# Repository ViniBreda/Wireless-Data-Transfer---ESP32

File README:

# Wireless Data Transfer Between two ESP32 - DOIT Devkit 1

* File upload via bluetooth available BUT VERY SLOW;
* The goal is to send a 500KB file from one ESP32 to another, atleast 100m apart;
* The PCB was of the transmission board was designed considering up to eight I²C devices connected to it so it works as a DataLogger;
* The receiver PCB is just a normal DOIT Devkit 1 remake to learn how to use KiCad;
* This is just a concept, not all funcionalities will be developed/tested as the main goal is to send a file over a Wireless Conection, one of them being battery powered.

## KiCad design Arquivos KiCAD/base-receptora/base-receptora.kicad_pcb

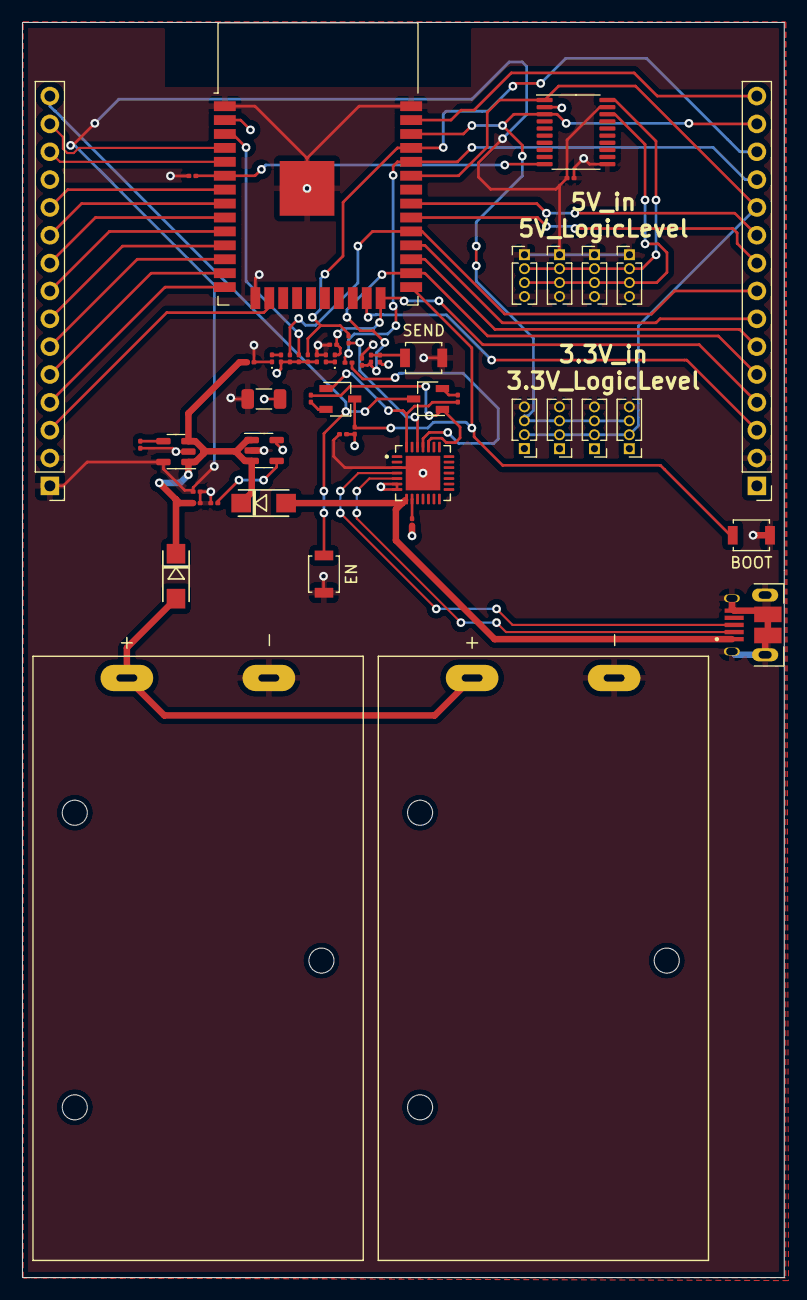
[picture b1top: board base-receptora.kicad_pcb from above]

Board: 4 copper layers, 69.5 x 114.5 mm, 52 parts (0 on the bottom side), 50 nets.

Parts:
BT1, BT2: BC9VPC; BAT_BC9VPC
C1: 2.2u; C_0201_0603Metric
C2, C4: 0.1u; C_0201_0603Metric
C3: 100uF/6.3V; C_1206_3216Metric
C5, C8: 1u; C_0201_0603Metric
C6, C9: 470p; C_0201_0603Metric
C7, C10: 10u; C_0201_0603Metric
D1: Azul; LED_0201_0603Metric
D2: Vermelho; LED_0201_0603Metric
D3, D4: SS14; DO-214AC
J1: 10103594-0001LF; AMPHENOL_10103594-0001LF
J2: I²C1-5VLL-5VPow; PinHeader_1x04_P1.27mm_Vertical
J3: I²C1-3.3VLL&Pow; PinHeader_1x04_P1.27mm_Vertical
J4, J7: Conn_01x15_Male; PinHeader_1x15_P2.54mm_Vertical
J5: I²C2-5VLL-5VPow; PinHeader_1x04_P1.27mm_Vertical
J6: I²C2-3.3VLL&Pow; PinHeader_1x04_P1.27mm_Vertical
J8: I²C3-5VLL-5VPow; PinHeader_1x04_P1.27mm_Vertical
J9: I²C3-3.3VLL&Pow; PinHeader_1x04_P1.27mm_Vertical
J10: I²C4-5VLL-5VPow; PinHeader_1x04_P1.27mm_Vertical
J11: I²C4-3.3VLL&Pow; PinHeader_1x04_P1.27mm_Vertical
Q1, Q2: S8050; TSOT-23
R1, R2, R3, R10: 1K; R_0201_0603Metric
R4, R5, R6, R7, R8, R9, R14: 10K; R_0201_0603Metric
R11: 4.7K; R_0201_0603Metric
R12: 10k; R_0201_0603Metric
R13: 100; R_0201_0603Metric
R15: 2.2K; R_0201_0603Metric
SW1: EN; SW_SPST_B3U-1000P
SW2: BOOT; SW_SPST_B3U-1000P
SW3: SEND; SW_SPST_B3U-1000P
U1: CP2102-GM; QFN50P500X500X100-29N
U2: ESP32-WROOM-32
U3: TXS0108EPW; TSSOP-20_4.4x6.5mm_P0.65mm
U4: SPX3819M5-L-5-0; SOT-23-5
U5: SPX3819M5-L-3-3; SOT-23-5

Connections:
+3V3: C2.1, C3.1, C10.1, J3.1, J6.1, J7.1, J9.1, J11.1, R2.1, R6.1, R7.1, R9.1, R11.2, R12.2, R14.1, U1.6 (VDD), U1.7 (REGIN), U2.2 (VDD), U3.2 (VCCA), U5.5 (OUT)
+5V: C4.1, C7.1, J2.1, J4.1, J5.1, J8.1, J10.1, U3.19 (VCCB), U4.5 (OUT)
+BATT: BT1.P, BT2.P, D3.A
-BATT: BT1.N, BT2.N, C1.2, C2.2, C3.2, C4.2, C5.2, C6.2, C7.2, C8.2, C9.2, C10.2, D2.1 (K), J1.5 (GND), J1.6 (SHIELD), J1.7 (SHIELD), J1.8 (SHIELD), J1.9 (SHIELD), J1.10 (SHIELD), J1.11 (SHIELD), J1.S1 (SHIELD), J1.S2 (SHIELD), J2.4, J3.4, J4.2, J5.4, J6.4, J7.2, J8.4, J9.4, J10.4, J11.4, R1.1, R8.1, R15.2, SW1.2, SW2.2, SW3.1, U1.3 (GND), U1.29 (GND), U2.1 (GND), U2.15 (GND), U2.38 (GND), U2.39 (GND), U3.11 (GND), U4.2 (GND), U5.2 (GND)
/5VLL_SCL: J2.3, J5.3, J8.3, J10.3, U3.18 (B2)
/5VLL_SDA: J2.2, J5.2, J8.2, J10.2, U3.20 (B1)
/A4: J4.10, U2.8 (IO32)
/A5: J4.9, U2.9 (IO33)
/A7: J4.11, U2.7 (IO35)
/A8: J4.8, U2.10 (IO25)
/A9: J4.7, U2.11 (IO26)
/D+: J1.3 (D+), U1.4 (D+)
/D-: J1.2 (D-), U1.5 (D–)
/DTR: Q2.1 (E), R4.2, U1.28 (~DTR)
/EN: J4.15, Q1.3 (C), SW1.1
/GPIO0: Q2.3 (C), R9.2, SW2.1, U2.25 (IO0)
/GPIO2: D1.2 (A), J7.4, R8.2, U2.24 (IO2)
/GPIO4: C1.1, J7.5, R13.1, U2.26 (IO4)
/GPIO5: J7.8, R6.2, U2.29 (IO5)
/GPIO12: J4.4, U2.14 (IO12)
/GPIO13: J4.3, U2.16 (IO13)
/GPIO14: J4.5, U2.13 (IO14)
/GPIO15: J7.3, U2.23 (IO15)
/GPIO18: J7.9, U2.30 (IO18)
/GPIO19: J7.10, U2.31 (IO19)
/GPIO21: J3.2, J6.2, J7.11, J9.2, J11.2, U2.33 (IO21), U3.1 (A1)
/GPIO22: J3.3, J6.3, J7.14, J9.3, J11.3, U2.36 (IO22), U3.3 (A2)
/GPIO23: J7.15, U2.37 (IO23)
/GPIO27: J4.6, U2.12 (IO27)
/I²C5VLLEnable: R15.1, U2.6 (IO34), U3.10 (OE)
/RTS: Q1.1 (E), R5.2, U1.24 (~RTS)
/RX0: J7.12, R10.2, U2.34 (RXD0/IO3)
/RX2: J7.6, U2.27 (IO16)
/TX0: J7.13, R3.1, R7.2, U2.35 (TXD0/IO1)
/TX2: J7.7, U2.28 (IO17)
/VN: J4.13, U2.5 (SENSOR_VN)
/VP: J4.14, U2.4 (SENSOR_VP)
unnamed: C6.1, U4.4 (BP)
unnamed: C9.1, U5.4 (BP)
unnamed: D1.1 (K), R1.2
unnamed: D2.2 (A), R2.2
unnamed: Q1.2 (B), R4.1
unnamed: Q2.2 (B), R5.1
unnamed: R3.2, U1.26 (TXD)
unnamed: R10.1, U1.25 (RXD)
unnamed: R11.1, U1.9 (~RST)
unnamed: R12.1, R13.2, SW3.2
unnamed: R14.2, U2.3 (EN)
VBUS: D4.A, J1.1 (VCC), U1.8 (VBUS)
VCC: C5.1, C8.1, D3.K, D4.K, U4.1 (IN), U4.3 (EN), U5.1 (IN), U5.3 (EN)

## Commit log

2022-03-28 Creating Repo
2022-03-28 Crating Repo
2022-03-28 Adição de README e Upload por Bluetooth funcional
2022-03-28 Correções no readme
2022-03-28 Added LITTLEFS Helper files
2022-03-28 Remove LITTLEFS.h from main
2022-03-29 BT toggle DONE
2022-03-30 Proper BT toggle starting off
2022-03-30 README Update
2022-03-30 Readme correction
2022-03-30 Add WiFi Station and GET Request setup
2022-03-30 Edit Flash memory size by removing WiFi programming
2022-03-31 Edit TODO on README
2022-03-31 both devices on the same code + HTPP server and client + soft AP for transmissor
2022-04-01 Properly Set Time Event and get Stations connected to AP
2022-04-01 define time intervall for get request and update readme
2022-04-01 Correct Time Management
2022-04-01 Proper Partitions Formatting and README update
2022-04-01 Properuse of device define and receiver test
2022-04-01 Proper HTTP Communication between boards
2022-04-03 Update recconection process after AP disconnection
2022-04-03 LongRange addition and reconnect after disconnection
2022-04-03 small correction to transmissor code
2022-04-03 Code Update to handle disconnection of client
2022-04-03 Remove autoreconnect part that isnt working
2022-04-03 Fixed reconnection, testint long range
2022-04-03 fixing BTTOGGLE bug on GPIO2, switching to GPIO4
2022-04-03 Add serial print to get request to know what's happening
2022-04-03 README update on LR and Normal WiFi tests
2022-04-04 Add project schematics and PCB design
2022-04-04 Project description PDF
2022-04-04 Updates to README.md
2022-04-04 Readme Updates
2022-04-04 Updates on README.md
2022-04-04 Updates on README
2022-04-04 README.md Update
2022-04-04 Image Resize and center
2022-04-04 Images Recize and Rescale
2022-04-04 Images Resize and Rescale
2022-04-04 images update
